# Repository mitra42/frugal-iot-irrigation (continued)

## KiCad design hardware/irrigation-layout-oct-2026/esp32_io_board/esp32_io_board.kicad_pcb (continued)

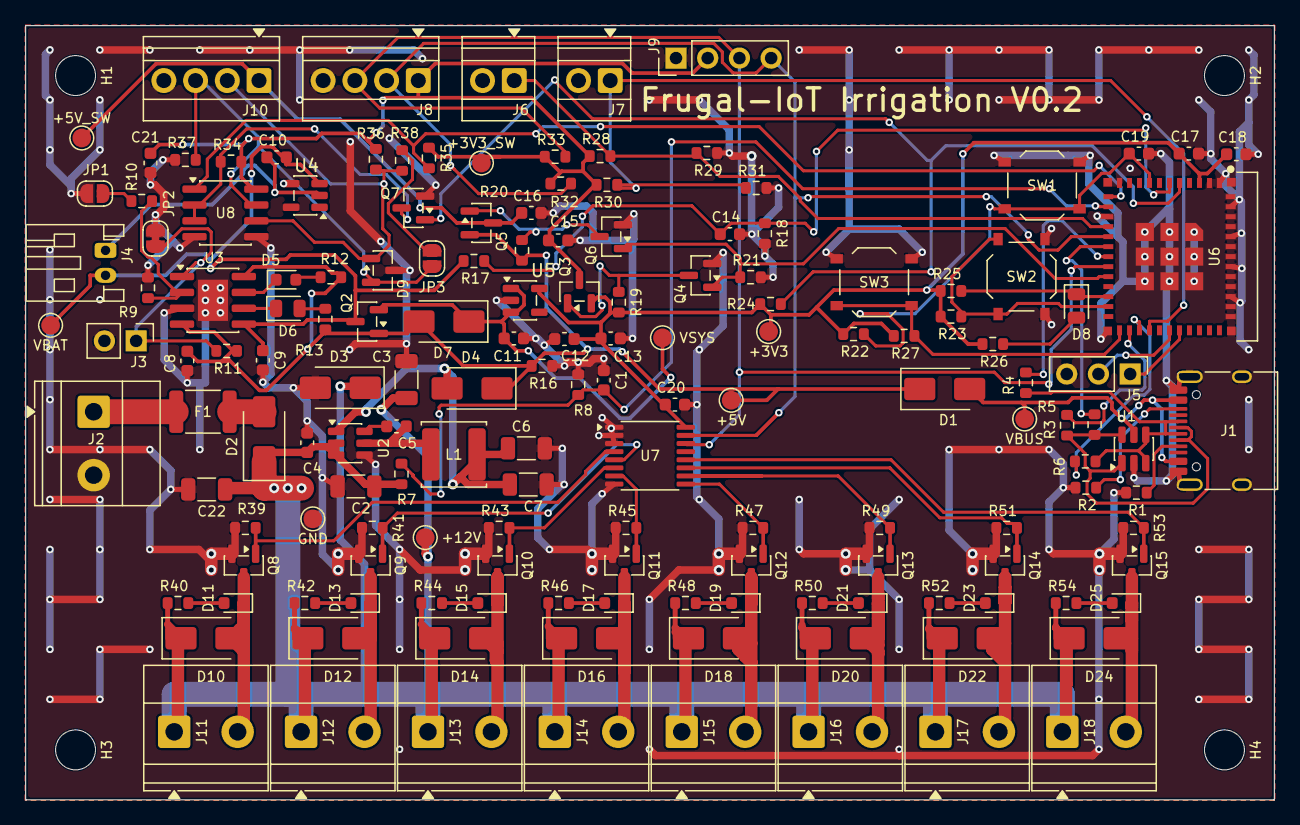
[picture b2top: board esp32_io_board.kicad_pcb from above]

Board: 2 copper layers, 100.0 x 62.0 mm, 160 parts (0 on the bottom side), 76 nets.

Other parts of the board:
H1, H2, H3, H4: M3; MountingHole_3.2mm_M3

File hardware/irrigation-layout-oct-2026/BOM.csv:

"Refs","Value","MPN","LCSC","Footprint","Qty","DNP","Note"
"C1,C4,C5,C10,C13,C14,C18,C20,C21","100nF","100nF","C14663","Capacitor_SMD:C_0603_1608Metric","9","",""
"C2,C3,C22","10uF 25V","10uF 25V","C13585","Capacitor_SMD:C_1206_3216Metric","3","",""
"C6,C7","22uF","22uF","C12891","Capacitor_SMD:C_1206_3216Metric","2","",""
"C8,C9,C11,C12,C16,C17","10uF","10uF","C19702","Capacitor_SMD:C_0603_1608Metric","6","",""
"C15,C19","1uF","1uF","C15849","Capacitor_SMD:C_0603_1608Metric","2","",""
"D1,D4,D7,D10,D12,D14,D16,D18,D20,D22,D24","SS34","SS34","C8678","Diode_SMD:D_SMA","11","",""
"D2","SS54","SS54","C22452","Diode_SMD:D_SMA","1","",""
"D3","SMAJ15A","SMAJ15A","C19077535","Diode_SMD:D_SMA","1","",""
"D5,D11,D13,D15,D17,D19,D21,D23,D25","RED","KT-0603R","C2286","LED_SMD:LED_0603_1608Metric","9","",""
"D6,D8","GREEN","KT-0805G","C2297","LED_SMD:LED_0805_2012Metric","2","",""
"D9","PSM712","PSM712-LF-T7","C32677","Package_TO_SOT_SMD:SOT-23","1","",""
"F1","3A 16V","SMD1812P300TF/16","C702820","Fuse:Fuse_1812_4532Metric","1","",""
"J1","USB-C","TYPE-C-31-M-12","C165948","Connector_USB:USB_C_Receptacle_HRO_TYPE-C-31-M-12","1","",""
"J2","12V IN","KF128-5.08-2P","C474952","irrigation:TerminalBlock_KF128-5.08-2P","1","",""
"J3","NTC","NTC","","Connector_PinHeader_2.54mm:PinHeader_1x02_P2.54mm_Vertical","1","DNP",""
"J4","LiPo","S2B-PH-K-S","C157932","Connector_JST:JST_PH_S2B-PH-K_1x02_P2.00mm_Horizontal","1","",""
"J5","UART0 debug","UART0 debug","","Connector_PinHeader_2.54mm:PinHeader_1x03_P2.54mm_Vertical","1","DNP",""
"J6","GPIO_A (C6)","XY308-2.54-2P","C557685","TerminalBlock:TerminalBlock_Xinya_XY308-2.54-2P_1x02_P2.54mm_Horizontal","1","",""
"J7","GPIO_B (C6)","XY308-2.54-2P","C557685","TerminalBlock:TerminalBlock_Xinya_XY308-2.54-2P_1x02_P2.54mm_Horizontal","1","",""
"J8","I2C sensor","XY308-2.54-4P","C915913","TerminalBlock:TerminalBlock_Xinya_XY308-2.54-4P_1x04_P2.54mm_Horizontal","1","",""
"J9","OLED","PZ254V-11-04P","C492403","Connector_PinHeader_2.54mm:PinHeader_1x04_P2.54mm_Vertical","1","",""
"J10","RS485","XY308-2.54-4P","C915913","TerminalBlock:TerminalBlock_Xinya_XY308-2.54-4P_1x04_P2.54mm_Horizontal","1","",""
"J11","Valve 1","KF128-5.08-2P","C474952","irrigation:TerminalBlock_KF128-5.08-2P","1","",""
"J12","Valve 2","KF128-5.08-2P","C474952","irrigation:TerminalBlock_KF128-5.08-2P","1","",""
"J13","Valve 3","KF128-5.08-2P","C474952","irrigation:TerminalBlock_KF128-5.08-2P","1","",""
"J14","Valve 4","KF128-5.08-2P","C474952","irrigation:TerminalBlock_KF128-5.08-2P","1","",""
"J15","Valve 5","KF128-5.08-2P","C474952","irrigation:TerminalBlock_KF128-5.08-2P","1","",""
"J16","Valve 6","KF128-5.08-2P","C474952","irrigation:TerminalBlock_KF128-5.08-2P","1","",""
"J17","Valve 7","KF128-5.08-2P","C474952","irrigation:TerminalBlock_KF128-5.08-2P","1","",""
"J18","Valve 8","KF128-5.08-2P","C474952","irrigation:TerminalBlock_KF128-5.08-2P","1","",""
"JP1","500mA","500mA","","Jumper:SolderJumper-2_P1.3mm_Open_RoundedPad1.0x1.5mm","1","",""
"JP2","NO_NTC","NO_NTC","","Jumper:SolderJumper-2_P1.3mm_Bridged_RoundedPad1.0x1.5mm","1","",""
"JP3","TERM","TERM","","Jumper:SolderJumper-2_P1.3mm_Open_RoundedPad1.0x1.5mm","1","",""
"L1","4.7uH","SWPA5040S4R7NT","C305174","Inductor_SMD:L_Sunlord_SWPA5040S","1","",""
"Q2,Q3,Q5","AO3401A","AO3401A","C15127","Package_TO_SOT_SMD:SOT-23","3","",""
"Q4,Q6,Q7","2N7002","2N7002","C8545","Package_TO_SOT_SMD:SOT-23","3","",""
"Q8-Q15","AO3400A","AO3400A","C20917","Package_TO_SOT_SMD:SOT-23","8","",""
"R1,R2","5.1k","5.1k","C23186","Resistor_SMD:R_0603_1608Metric","2","",""
"R3,R4","0R","0R","C21189","Resistor_SMD:R_0603_1608Metric","2","","Fit for C6 module"
"R5,R6","0R","0R","C21189","Resistor_SMD:R_0603_1608Metric","2","DNP","Fit for C3 module"
"R7","560k","560k","C23203","Resistor_SMD:R_0603_1608Metric","1","",""
"R8,R16,R19-R21,R39,R41,R43,R45,R47,R49,R51,R53","100k","100k","C25803","Resistor_SMD:R_0603_1608Metric","13","","rails off at reset,valve off at reset"
"R9,R10,R32,R33,R40,R42,R44,R46,R48,R50,R52,R54","4.7k","4.7k","C23162","Resistor_SMD:R_0603_1608Metric","12","","with JP: ~500 mA,~250 mA"
"R11,R28-R31","10k","10k","C25804","Resistor_SMD:R_0603_1608Metric","5","DNP","NTC divider, value per cell NTC,pull-down option,pull-up option"
"R12,R13,R26","1k","1k","C21190","Resistor_SMD:R_0603_1608Metric","3","",""
"R17,R18","1M","1M","C22935","Resistor_SMD:R_0603_1608Metric","2","",""
"R22-R25,R27,R34,R35","10k","10k","C25804","Resistor_SMD:R_0603_1608Metric","7","","GPIO8 strap high,also C3 GPIO2 strap high"
"R36,R37","680R","680R","C23228","Resistor_SMD:R_0603_1608Metric","2","","bias"
"R38","120R","120R","C22787","Resistor_SMD:R_0603_1608Metric","1","",""
"SW1","RESET","TS-1187A-B-A-B","C318884","Button_Switch_SMD:SW_Push_1P1T_XKB_TS-1187A","1","",""
"SW2","BOOT / BTN1","TS-1187A-B-A-B","C318884","Button_Switch_SMD:SW_Push_1P1T_XKB_TS-1187A","1","",""
"SW3","BTN2 (C6)","TS-1187A-B-A-B","C318884","Button_Switch_SMD:SW_Push_1P1T_XKB_TS-1187A","1","",""
"TP1","+12V","+12V","","TestPoint:TestPoint_Pad_D1.5mm","1","",""
"TP2","+5V","+5V","","TestPoint:TestPoint_Pad_D1.5mm","1","",""
"TP3","VBUS","VBUS","","TestPoint:TestPoint_Pad_D1.5mm","1","",""
"TP4","VBAT","VBAT","","TestPoint:TestPoint_Pad_D1.5mm","1","",""
"TP5","VSYS","VSYS","","TestPoint:TestPoint_Pad_D1.5mm","1","",""
"TP6","+3V3","+3V3","","TestPoint:TestPoint_Pad_D1.5mm","1","",""
"TP7","+3V3_SW","+3V3_SW","","TestPoint:TestPoint_Pad_D1.5mm","1","",""
"TP8","+5V_SW","+5V_SW","","TestPoint:TestPoint_Pad_D1.5mm","1","",""
"TP9","GND","GND","","TestPoint:TestPoint_Pad_D1.5mm","1","",""
"U1","USBLC6-2SC6","USBLC6-2SC6","C7519","Package_TO_SOT_SMD:SOT-23-6","1","",""
"U2","AP63205WU","AP63205WU-7","C2071056","Package_TO_SOT_SMD:TSOT-23-6","1","",""
"U3","TP4056","TP4056","C16581","Package_SO:SOIC-8-1EP_3.9x4.9mm_P1.27mm_EP2.41x3.3mm","1","",""
"U4","XB5353A","XB5353A","C80628","Package_TO_SOT_SMD:SOT-23-5","1","",""
"U5","RT9080-33GJ5","RT9080-33GJ5","C841192","Package_TO_SOT_SMD:TSOT-23-5","1","",""
"U6","ESP32-C6-MINI-1U-H4 (alt C3-MINI-1U)","ESP32-C6-MINI-1U-H4","C20627095","irrigation:ESP32-C3-C6-MINI-1U","1","",""
"U7","TCA9534PWR","TCA9534PWR","C783615","Package_SO:TSSOP-16_4.4x5mm_P0.65mm","1","",""
"U8","SP3485EN","SP3485EN-L/TR","C8963","Package_SO:SOIC-8_3.9x4.9mm_P1.27mm","1","",""

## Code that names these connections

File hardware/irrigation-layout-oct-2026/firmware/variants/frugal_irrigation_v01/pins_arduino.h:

// Frugal-IoT Irrigation V0.1 - ESP32-C6-MINI-1U module (DECISIONS D18).
// Based on arduino-esp32 variants/esp32c6. Differences: LED_BUILTIN is a plain LED on GPIO8,
// active LOW (to +3V3 through 1k) - not the DevKit's RGB LED; SDA/SCL are this board's I2C pins.
#ifndef Pins_Arduino_h
#define Pins_Arduino_h

#include <stdint.h>
#include "soc/soc_caps.h"

static const uint8_t LED_BUILTIN = 8;   // D8 green, active LOW - build with -D ACTUATOR_LEDBUILTIN_INVERT
#define BUILTIN_LED LED_BUILTIN         // backward compatibility
#define LED_BUILTIN LED_BUILTIN         // allow testing #ifdef LED_BUILTIN

static const uint8_t TX = 16;           // UART0, unfitted debug header J5
static const uint8_t RX = 17;

static const uint8_t SDA = 7;           // pad 16; pull-ups on 3V3_SW
static const uint8_t SCL = 14;          // pad 19

// SPI is not used on this board; generic C6 defaults kept so libraries that expect them compile.
static const uint8_t SS = 18;
static const uint8_t MOSI = 19;         // also BTN2
static const uint8_t MISO = 20;
static const uint8_t SCK = 21;

static const uint8_t A0 = 0;            // RS485 RX
static const uint8_t A1 = 1;            // V12_SENSE (12 V in x 100k/660k)
static const uint8_t A2 = 2;            // RS485 TX
static const uint8_t A3 = 3;            // VBAT_SENSE (cell / 2)
static const uint8_t A4 = 4;
static const uint8_t A5 = 5;
static const uint8_t A6 = 6;            // GPIO_A terminal

// LP I2C pins are fixed on ESP32-C6
#define WIRE1_PIN_DEFINED
static const uint8_t SDA1 = 6;
static const uint8_t SCL1 = 7;

#endif /* Pins_Arduino_h */

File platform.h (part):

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#if defined(S2_MINI_DAUGHTER)
  #define FRUGAL_IOT_BOARD_CONFIGURED
  #define SYSTEM_OTA_SUFFIX "s2_mini_daughter"
  #define I2C_SDA 16
  #define I2C_SCL 18
  #define IRRIGATION_RELAY_TCA9534_ADDRESS 0x20
  #define IRRIGATION_VALVE1_BIT 0 // daughter J4
  #define IRRIGATION_VALVE2_BIT 1 // daughter J5
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    #error "Set Tools > USB CDC On Boot > Enabled - this board has no USB-serial chip, so without it the Serial Monitor stays empty"
  #endif
  #define ACTUATOR_LEDBUILTIN_INVERT // status LED D8 on GPIO8 is active LOW
  #define I2C_SDA 7
  #define I2C_SCL 14
  #define SYSTEM_POWER3v3_PIN 15
  #define SYSTEM_RS485_RX_PIN 0
  #define SYSTEM_RS485_TX_PIN 2
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  // #define IRRIGATION_VALVE5_BIT 5 // J16
  // #define IRRIGATION_VALVE6_BIT 6 // J17
  // #define IRRIGATION_VALVE7_BIT 7 // J18
  // #define SENSOR_TANK_PIN 6 // GPIO_A terminal J6 (ADC1_CH6) - e.g. the tank gauge
  #define ACTUATOR_OLED_WANT
  #define ACTUATOR_OLED_IS_SSD1306
  #define OLED_WIRE Wire
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  #if !ARDUINO_USB_CDC_ON_BOOT // Serial = USB
    #error "Set Tools > USB CDC On Boot > Enabled - this board has no USB-serial chip, so without it the Serial Monitor stays empty"
  #endif
  #define I2C_SDA 6
  #define I2C_SCL 7
  #define SYSTEM_POWER0_PIN 5
  #define IRRIGATION_RELAY_TCA9534_ADDRESS 0x20
  #define IRRIGATION_VALVE1_BIT 0 // daughter J4
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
